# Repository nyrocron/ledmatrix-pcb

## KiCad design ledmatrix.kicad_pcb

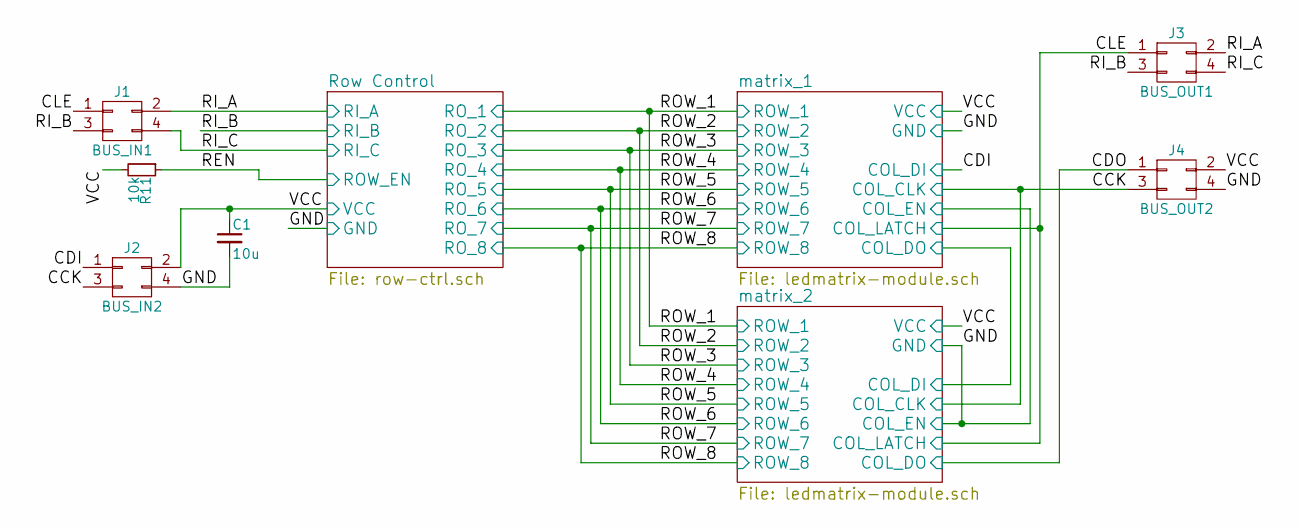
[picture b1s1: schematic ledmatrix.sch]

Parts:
C1: 10u; 0805_HAND
J1: BUS_IN1; PINHDR_2x2_angled_male
J2: BUS_IN2; PINHDR_2x2_angled_male
J3: BUS_OUT1; PINHDR_2x2_angled_female
J4: BUS_OUT2; PINHDR_2x2_angled_female
R11: 10k; 0603_HAND

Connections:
/CCK: J2.3, J4.3; also elsewhere on the board
/CDI: J2.1; also elsewhere on the board
/CDO: J4.1; also elsewhere on the board
/CLE: J1.1, J3.1; also elsewhere on the board
/GND: C1.2, J2.4, J4.4; also elsewhere on the board
/REN: R11.1; also elsewhere on the board
/RI_A: J1.2, J3.2; also elsewhere on the board
/RI_B: J1.3, J3.3; also elsewhere on the board
/RI_C: J1.4, J3.4; also elsewhere on the board
/VCC: C1.1, J2.2, J4.2, R11.2; also elsewhere on the board

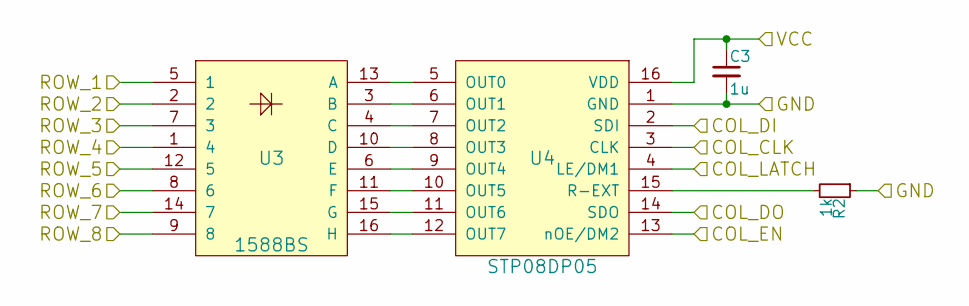
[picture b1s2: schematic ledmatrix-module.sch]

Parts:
C2: 1u; 0603_HAND
R1: 1k; 0603_HAND
U1: 1588BS; LEDMATRIX_1588BS
U2: STP08DP05; SO-16-N

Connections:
/CCK: U2.3 (CLK); also elsewhere on the board
/CDI: U2.2 (SDI); also elsewhere on the board
/CLE: U2.4 (LE/DM1); also elsewhere on the board
/GND: C2.2, R1.1, U2.1 (GND), U2.13 (nOE/DM2); also elsewhere on the board
/ROW_1: U1.5 (1); also elsewhere on the board
/ROW_2: U1.2; also elsewhere on the board
/ROW_3: U1.7 (3); also elsewhere on the board
/ROW_4: U1.1 (4); also elsewhere on the board
/ROW_5: U1.12 (5); also elsewhere on the board
/ROW_6: U1.8 (6); also elsewhere on the board
/ROW_7: U1.14 (7); also elsewhere on the board
/ROW_8: U1.9 (8); also elsewhere on the board
/VCC: C2.1, U2.16 (VDD); also elsewhere on the board
/matrix_2/COL_DI: U2.14 (SDO); also elsewhere on the board
unnamed: R1.2, U2.15 (R-EXT)
unnamed: U1.3 (B), U2.6 (OUT1)
unnamed: U1.4 (C), U2.7 (OUT2)
unnamed: U1.6 (E), U2.9 (OUT4)
unnamed: U1.10 (D), U2.8 (OUT3)
unnamed: U1.11 (F), U2.10 (OUT5)
unnamed: U1.13 (A), U2.5 (OUT0)
unnamed: U1.15 (G), U2.11 (OUT6)
unnamed: U1.16 (H), U2.12 (OUT7)

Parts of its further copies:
C3: 1u; 0603_HAND
R2: 1k; 0603_HAND
U3, U6: 1588BS; LEDMATRIX_1588BS
U4, U7: STP08DP05; SO-16-N

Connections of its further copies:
/CCK: U4.3 (CLK); also elsewhere on the board
/CDO: U4.14 (SDO); also elsewhere on the board
/CLE: U4.4 (LE/DM1); also elsewhere on the board
/GND: C3.2, R2.1, U4.1 (GND), U4.13 (nOE/DM2); also elsewhere on the board
/ROW_1: U3.5 (1); also elsewhere on the board
/ROW_2: U3.2; also elsewhere on the board
/ROW_3: U3.7 (3); also elsewhere on the board
/ROW_4: U3.1 (4); also elsewhere on the board
/ROW_5: U3.12 (5); also elsewhere on the board
/ROW_6: U3.8 (6); also elsewhere on the board
/ROW_7: U3.14 (7); also elsewhere on the board
/ROW_8: U3.9 (8); also elsewhere on the board
/VCC: C3.1, U4.16 (VDD); also elsewhere on the board
/matrix_2/COL_DI: U4.2 (SDI); also elsewhere on the board
unnamed: R2.2, U4.15 (R-EXT)
unnamed: U3.3 (B), U4.6 (OUT1)
unnamed: U3.4 (C), U4.7 (OUT2)
unnamed: U3.6 (E), U4.9 (OUT4)
unnamed: U3.10 (D), U4.8 (OUT3)
unnamed: U3.11 (F), U4.10 (OUT5)
unnamed: U3.13 (A), U4.5 (OUT0)
unnamed: U3.15 (G), U4.11 (OUT6)
unnamed: U3.16 (H), U4.12 (OUT7)

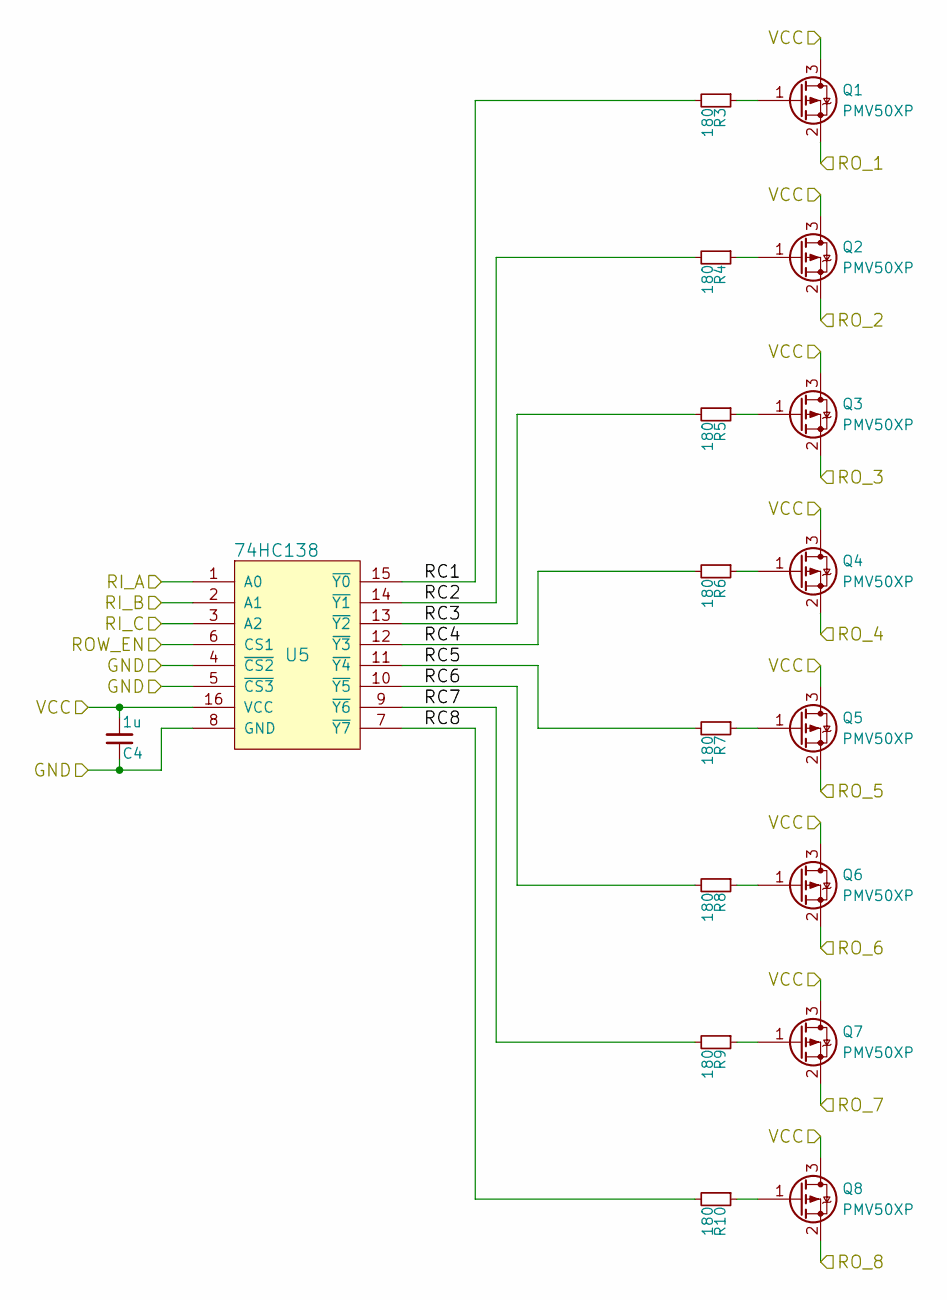
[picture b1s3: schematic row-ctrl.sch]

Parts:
C4: 1u; 0603_HAND
Q1, Q2, Q3, Q4, Q5, Q6, Q7, Q8: PMV50XP; SOT-23_Handsoldering
R3, R4, R5, R6, R7, R8, R9, R10: 180; 0603_HAND
U5: 74HC138; SOIC-16

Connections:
/GND: C4.1, U5.4 (~CS2), U5.5 (~CS3), U5.8 (GND); also elsewhere on the board
/REN: U5.6 (CS1); also elsewhere on the board
/RI_A: U5.1 (A0); also elsewhere on the board
/RI_B: U5.2 (A1); also elsewhere on the board
/RI_C: U5.3 (A2); also elsewhere on the board
/ROW_1: Q1.2 (S); also elsewhere on the board
/ROW_2: Q2.2 (S); also elsewhere on the board
/ROW_3: Q3.2 (S); also elsewhere on the board
/ROW_4: Q4.2 (S); also elsewhere on the board
/ROW_5: Q5.2 (S); also elsewhere on the board
/ROW_6: Q6.2 (S); also elsewhere on the board
/ROW_7: Q7.2 (S); also elsewhere on the board
/ROW_8: Q8.2 (S); also elsewhere on the board
/Row Control/RC1: R3.2, U5.15 (~Y0)
/Row Control/RC2: R4.2, U5.14 (~Y1)
/Row Control/RC3: R5.2, U5.13 (~Y2)
/Row Control/RC4: R6.2, U5.12 (~Y3)
/Row Control/RC5: R7.2, U5.11 (~Y4)
/Row Control/RC6: R8.2, U5.10 (~Y5)
/Row Control/RC7: R9.2, U5.9 (~Y6)
/Row Control/RC8: R10.2, U5.7 (~Y7)
/VCC: C4.2, Q1.3 (D), Q2.3 (D), Q3.3 (D), Q4.3 (D), Q5.3 (D), Q6.3 (D), Q7.3 (D), Q8.3 (D), U5.16 (VCC); also elsewhere on the board
unnamed: Q1.1 (G), R3.1
unnamed: Q2.1 (G), R4.1
unnamed: Q3.1 (G), R5.1
unnamed: Q4.1 (G), R6.1
unnamed: Q5.1 (G), R7.1
unnamed: Q6.1 (G), R8.1
unnamed: Q7.1 (G), R9.1
unnamed: Q8.1 (G), R10.1

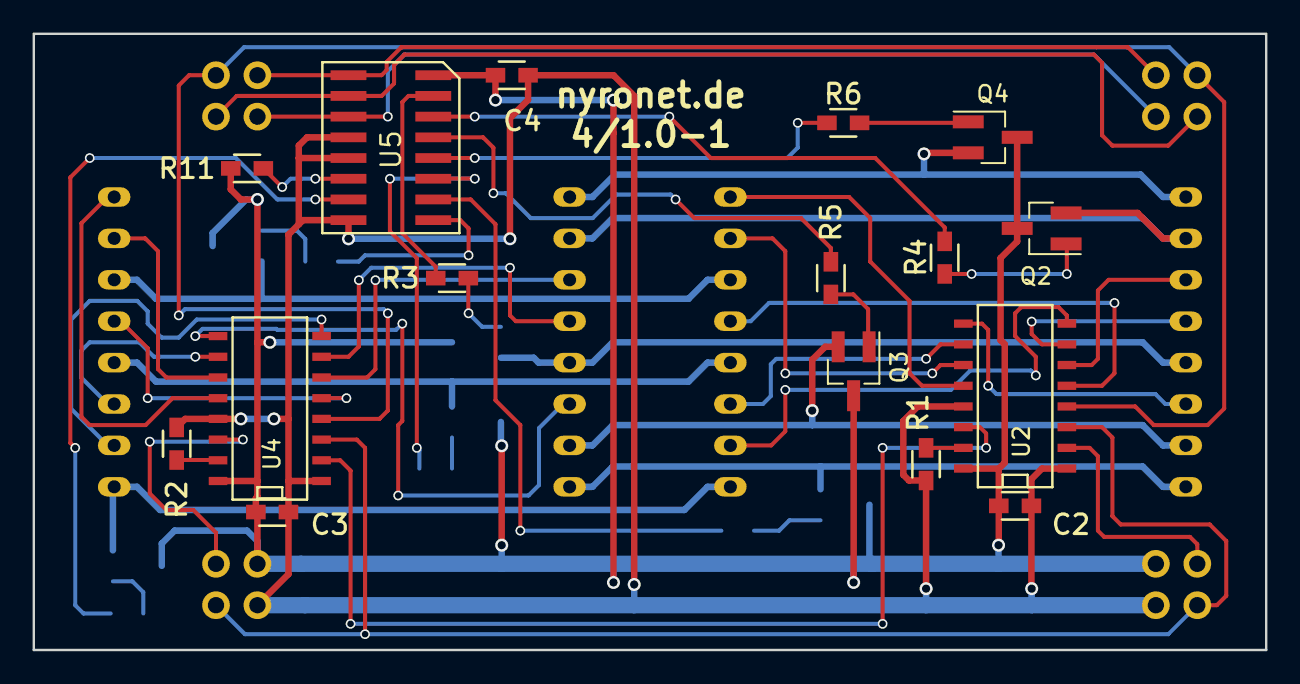
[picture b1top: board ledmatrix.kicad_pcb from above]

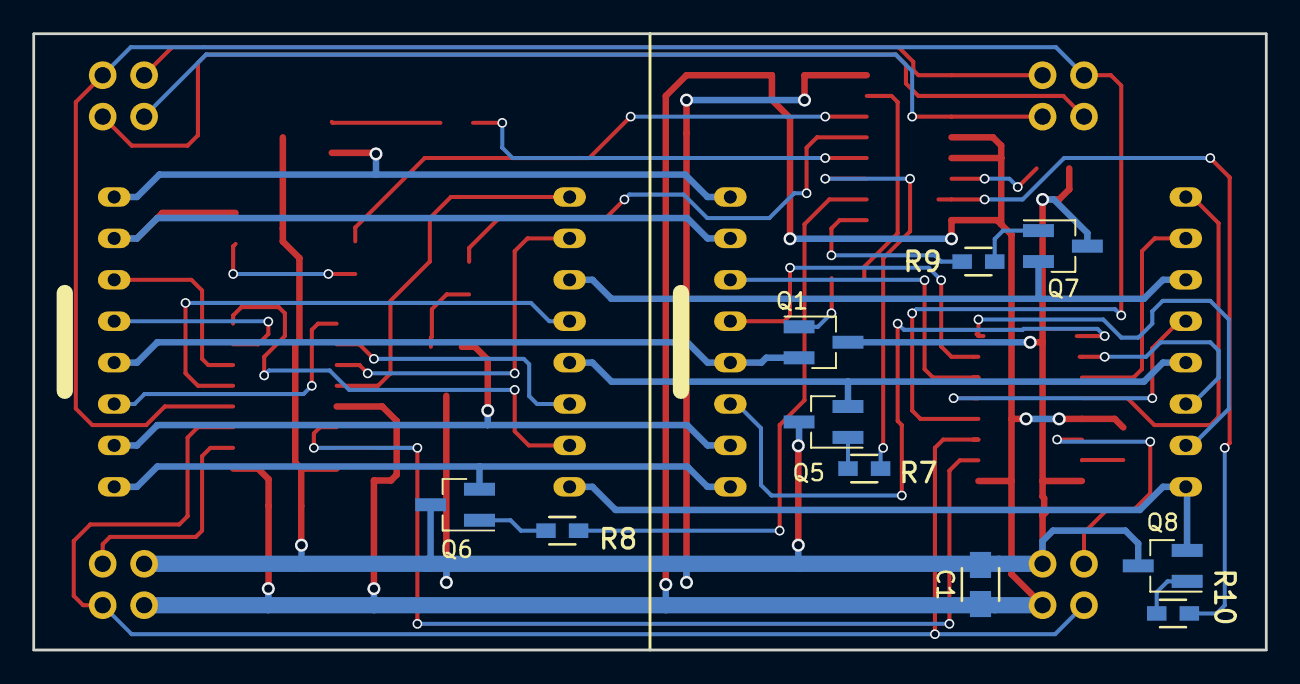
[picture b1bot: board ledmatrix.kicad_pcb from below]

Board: 2 copper layers, 75.6 x 37.8 mm, 32 parts (12 on the bottom side), 53 nets.

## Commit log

2017-09-02 rename project to ledmatrix
2017-09-02 dual matrix with 2x2 interconnects
2017-09-02 fix matrix module order
2017-09-02 cleaner vcc, gnd on left side
2017-09-02 finish left side traces
2017-09-02 save schematic changes
2017-09-03 add bypassing to schematic
2017-09-03 read bypassing netlist into pcbnew
2017-09-03 fully connected PCB
2017-09-03 move R3 driver closer to R3
2017-09-03 generale gerbers
2017-09-07 adjust silkscreen
